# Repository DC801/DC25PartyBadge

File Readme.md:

# DC801_DC25PartyBadge
Party badge and BLE hardware board

Photo credits to [Cat Murdock](https://twitter.com/catmurd0ck), thank you!

# Hardware
 - **Rigado BMD-300** Bluetooth low energy based on a Nordic nRF52832
   - 16MHz ARM® Cortex™ M4F CPU, 512kB of flash memory, 64kB RAM
   - [https://www.rigado.com/product/bmd-300/](https://www.rigado.com/product/bmd-300/)
 ***
 - **Lots of I/O**
   - 2 RGB LEDs (_eyes_)
   - 7 yellow LEDs (_helmet_)
   - 6 red LEDs (_helmet wings_)
   - Speaker
   - 4 buttons
   - 2 capacitive 'touch' buttons (_for you to discover_)
   - SPI LCD screen
   - Selected pin breakouts
   - JTAG interface
   - Micro USB - for charging only
 ***
 - A MCP73831 LiPo battery charger
 - Kickass silkscreen

Board design is in Eagle

See the [Hardware](/Hardware) directory for more info, schematics and etc

# Software
Environment is Eclipse with the GNU ARM GCC
Need a J-Link Segger JTAG programmer
Uses the softdevice s132

See the [Software](/Software) directory for more info

# What's it do?

Awesome **things**, that's what!  See the [Software](Software) directory for more information.

# More info

Follow [@rushan_ee](http://twitter.com/rushan_ee) or [@hamster](http://twitter.com/hamster) for updates

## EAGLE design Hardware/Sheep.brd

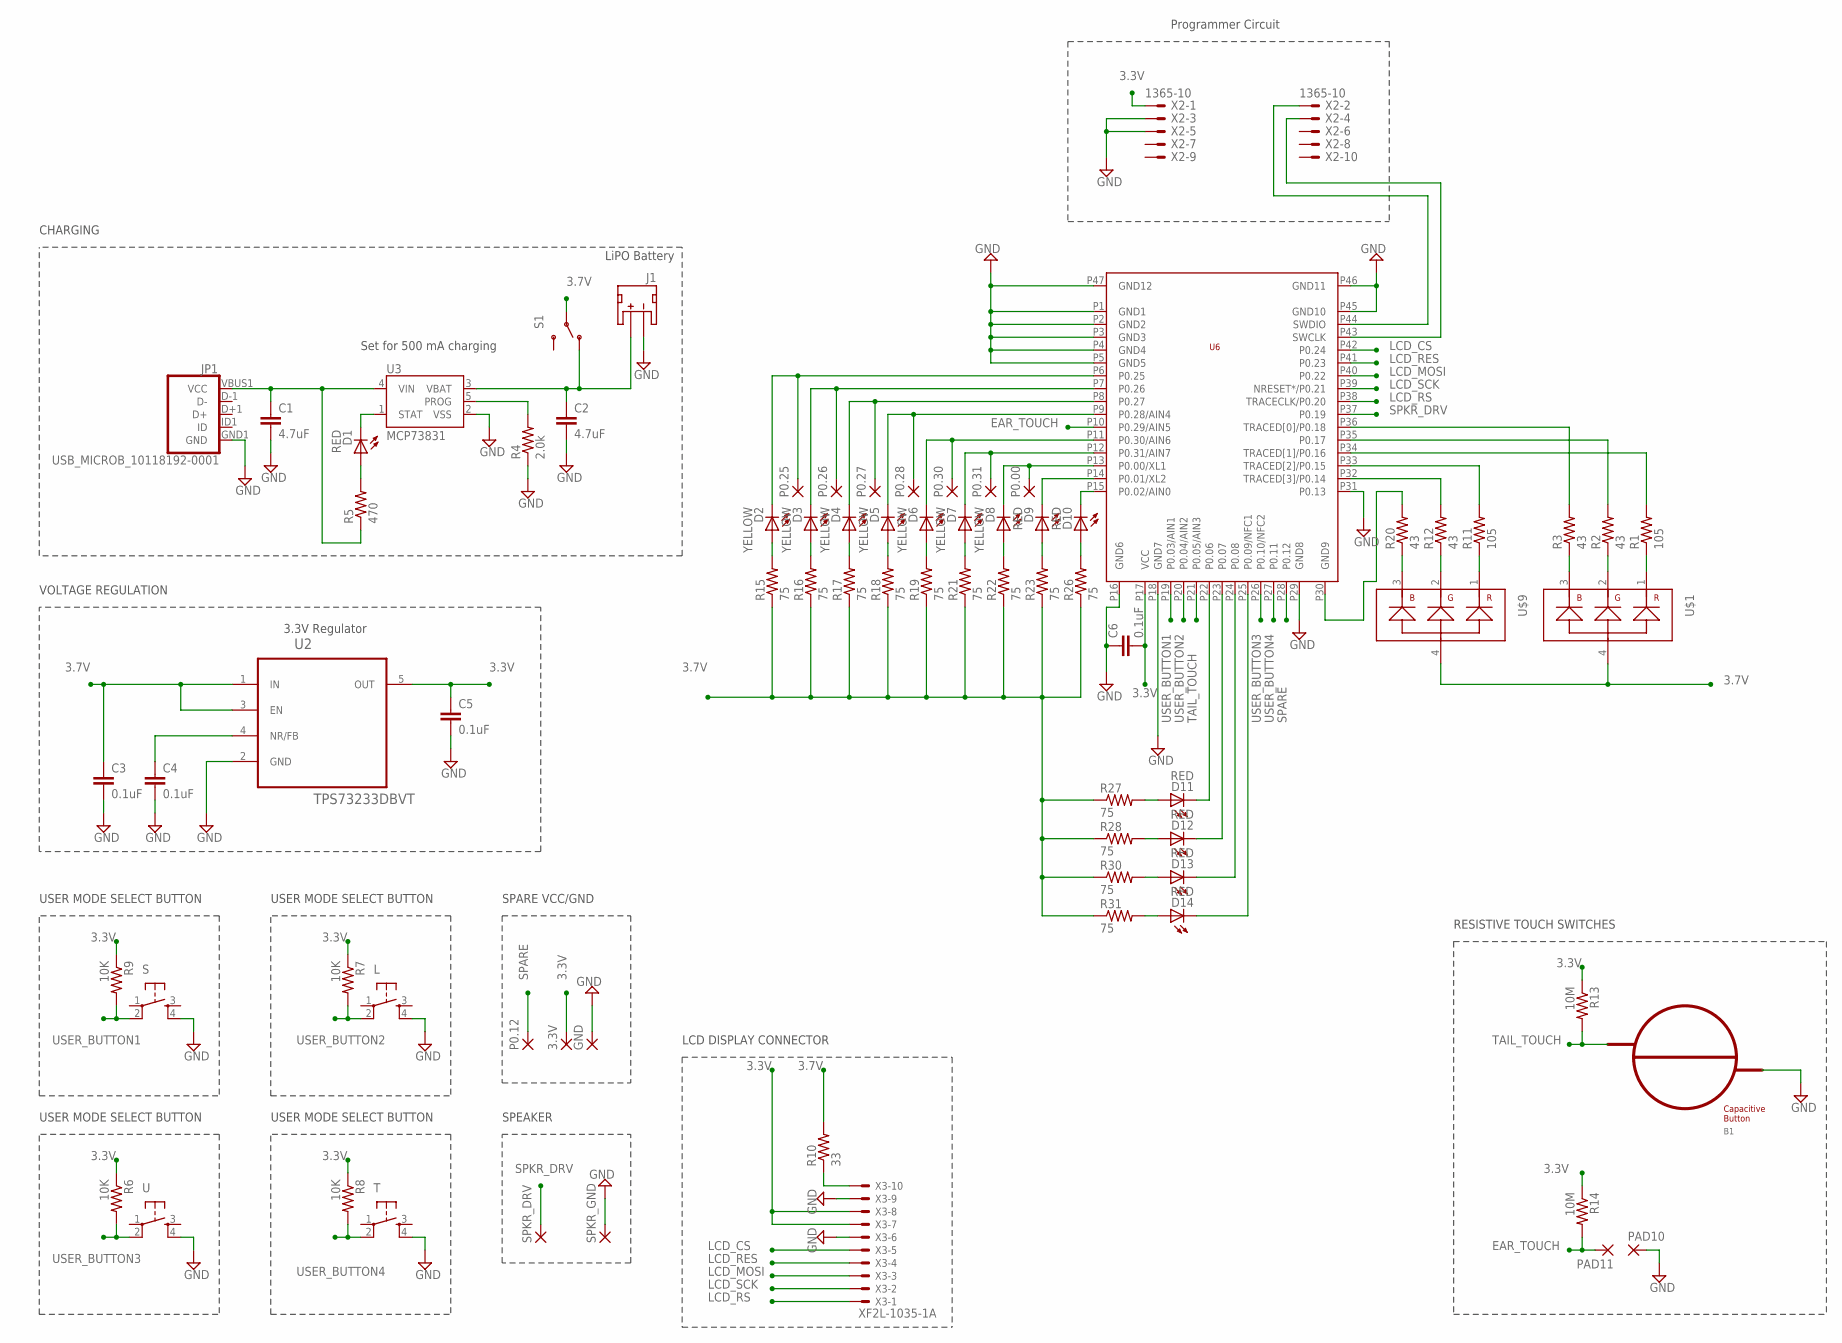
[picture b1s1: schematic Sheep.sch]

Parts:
3.3V: 1,6/0,8
B1: BUTTON_ACTIVE_DUAL; BUTTON_ACTIVE_DUAL_10MM
C1, C2: 4.7uF; 0603-CAP
C3, C4, C5, C6: 0.1uF; C0201
D1, D9, D10, D11, D12, D13, D14: RED; CHIP-LED0603
D2, D3, D4, D5, D6, D7, D8: YELLOW; CHIP-LED0603
GND: 1,6/0,8
J1: JST_2MM_MALE; JST-2-SMD
JP1: USB_MICROB_10118192-0001; USB-B-MICRO-SMD_V03
L: DTSM-6
P0.00, P0.12, P0.25, P0.26, P0.27, P0.28, P0.30, P0.31: 1,6/0,8
PAD10, PAD11: SMD5; SMD2,54-5,08
R1, R11: 105; R0201
R2, R3, R12, R20: 43; R0201
R4: 2.0k; R0201
R5: 470; R0201
R6, R7, R8, R9: 10K; R0201
R10: 33; R0201
R13, R14: 10M; R0201
R15, R16, R17, R18, R19, R21, R22, R23, R26, R27, R28, R30, R31: 75; R0201
S: DTSM-6
S1: SWITCH-SPDTSMD2; SWITCH-SPDT-SMD
SPKR_DRV: 1,6/0,8
SPKR_GND: 1,6/0,8
T: DTSM-6
U: DTSM-6
U2: TPS73233DBVT; SOT95P280X145-5N
U3: MCP73831; SOT23-5
U6: BMD-300
U$1, U$9: RGB; 0606
X2: 1365-10
X3: XF2L-1035-1A; 52745-1090

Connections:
3.3V: 3.3V.1, C5.1, C6.2, R6.1, R7.1, R8.1, R9.1, R13.1, R14.1, U2.5 (OUT), U6.P17 (VCC), X2.1, X3.7, X3.8
3.7V: C3.1, R10.2, R15.1, R16.1, R17.1, R18.1, R19.1, R21.1, R22.1, R23.1, R26.1, R27.1, R28.1, R30.1, R31.1, S1.2, U2.1 (IN), U2.3 (EN), U$1.4, U$9.4
5.0V: C1.1, JP1.VBUS1 (VCC), R5.1, U3.4 (VIN)
EAR_TOUCH: PAD11.1, R14.2, U6.P10 (P0.29/AIN5)
GND: B1.Q1, C1.2, C2.2, C3.2, C4.2, C5.2, C6.1, GND.1, J1.1 (-), JP1.GND1 (GND), L.4, PAD10.1, R4.1, S.4, SPKR_GND.1, T.4, U.4, U2.2 (GND), U3.2 (VSS), U6.P1 (GND1), U6.P2 (GND2), U6.P3 (GND3), U6.P4 (GND4), U6.P5 (GND5), U6.P16 (GND6), U6.P18 (GND7), U6.P29 (GND8), U6.P31 (P0.13), U6.P45 (GND10), U6.P46 (GND11), U6.P47 (GND12), X2.3, X2.5, X3.6, X3.9
LCD_CS: U6.P42 (P0.24), X3.5
LCD_MOSI: U6.P40 (P0.22), X3.3
LCD_RES: U6.P41 (P0.23), X3.4
LCD_RS: U6.P38 (TRACECLK/P0.20), X3.1
LCD_SCK: U6.P39 (NRESET*/P0.21), X3.2
unnamed: R2.2, U6.P35 (P0.17)
unnamed: R3.2, U6.P36 (TRACED[0]/P0.18)
unnamed: R11.2, U6.P33 (TRACED[2]/P0.15)
unnamed: D6.C, P0.30.1, U6.P11 (P0.30/AIN6)
unnamed: D2.C, P0.25.1, U6.P6 (P0.25)
unnamed: U6.P44 (SWDIO), X2.2
unnamed: R20.2, U6.P30 (GND9)
unnamed: D11.C, U6.P22 (P0.06)
unnamed: D12.C, U6.P23 (P0.07)
unnamed: U6.P43 (SWCLK), X2.4
unnamed: R1.2, U6.P34 (TRACED[1]/P0.16)
unnamed: R1.1, U$1.1
unnamed: R2.1, U$1.2
unnamed: R3.1, U$1.3
unnamed: D3.C, P0.26.1, U6.P7 (P0.26)
unnamed: D13.C, U6.P24 (P0.08)
unnamed: D5.C, P0.28.1, U6.P9 (P0.28/AIN4)
unnamed: D7.C, P0.31.1, U6.P12 (P0.31/AIN7)
unnamed: D8.C, P0.00.1, U6.P13 (P0.00/XL1)
unnamed: D9.C, U6.P14 (P0.01/XL2)
unnamed: D10.C, U6.P15 (P0.02/AIN0)
unnamed: D14.C, U6.P25 (P0.09/NFC1)
unnamed: R12.2, U6.P32 (TRACED[3]/P0.14)
unnamed: R4.2, U3.5 (PROG)
unnamed: D11.A, R27.2
unnamed: D12.A, R28.2
unnamed: D13.A, R30.2
unnamed: D14.A, R31.2
unnamed: R10.1, X3.10
unnamed: D1.A, R5.2
unnamed: D1.C, U3.1 (STAT)
unnamed: R11.1, U$9.1
unnamed: R12.1, U$9.2
unnamed: D2.A, R15.2
unnamed: D3.A, R16.2
unnamed: D4.A, R17.2
unnamed: D5.A, R18.2
unnamed: D6.A, R19.2
unnamed: D7.A, R21.2
unnamed: D8.A, R22.2
unnamed: C4.1, U2.4 (NR/FB)
unnamed: D9.A, R23.2
unnamed: D10.A, R26.2
unnamed: R20.1, U$9.3
unnamed: D4.C, P0.27.1, U6.P8 (P0.27)
SPARE: P0.12.1, U6.P28 (P0.12)
SPKR_DRV: SPKR_DRV.1, U6.P37 (P0.19)
TAIL_TOUCH: B1.Q2, R13.2, U6.P21 (P0.05/AIN3)
USER_BUTTON1: R9.2, S.2, U6.P19 (P0.03/AIN1)
USER_BUTTON2: L.2, R7.2, U6.P20 (P0.04/AIN2)
USER_BUTTON3: R6.2, U.2, U6.P26 (P0.10/NFC2)
USER_BUTTON4: R8.2, T.2, U6.P27 (P0.11)
VBAT1: C2.1, J1.2 (+), S1.1 (O), U3.3 (VBAT)

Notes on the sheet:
LiPO Battery
Set for 500 mA charging
3.3V Regulator
CHARGING
VOLTAGE REGULATION
USER MODE SELECT BUTTON
Programmer Circuit
LCD DISPLAY CONNECTOR
SPARE VCC/GND
SPEAKER
RESISTIVE TOUCH SWITCHES

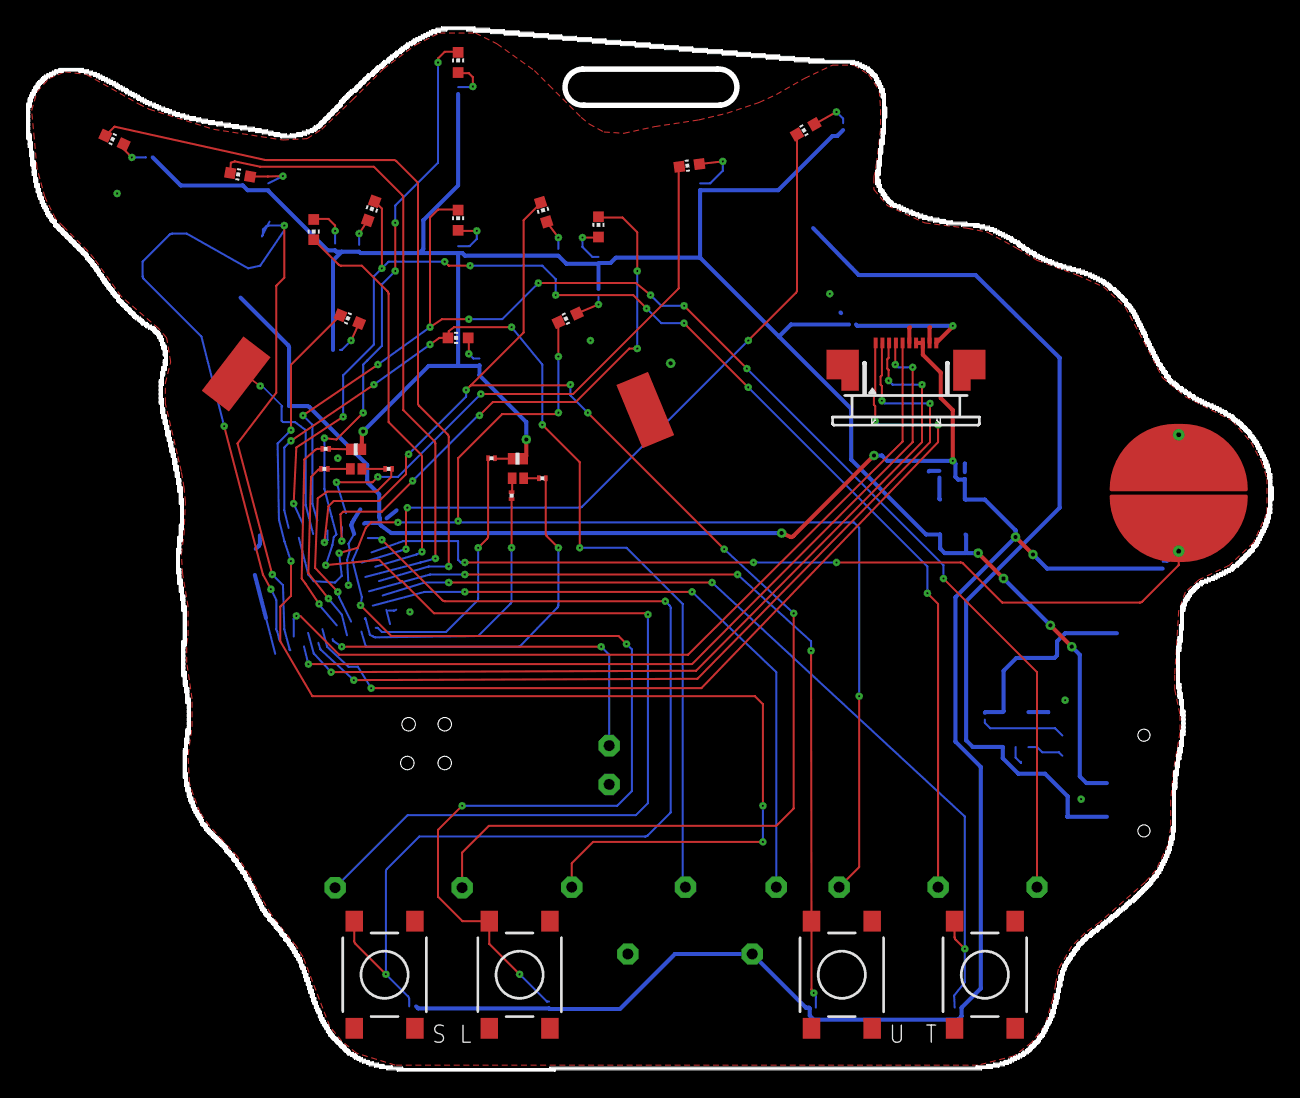
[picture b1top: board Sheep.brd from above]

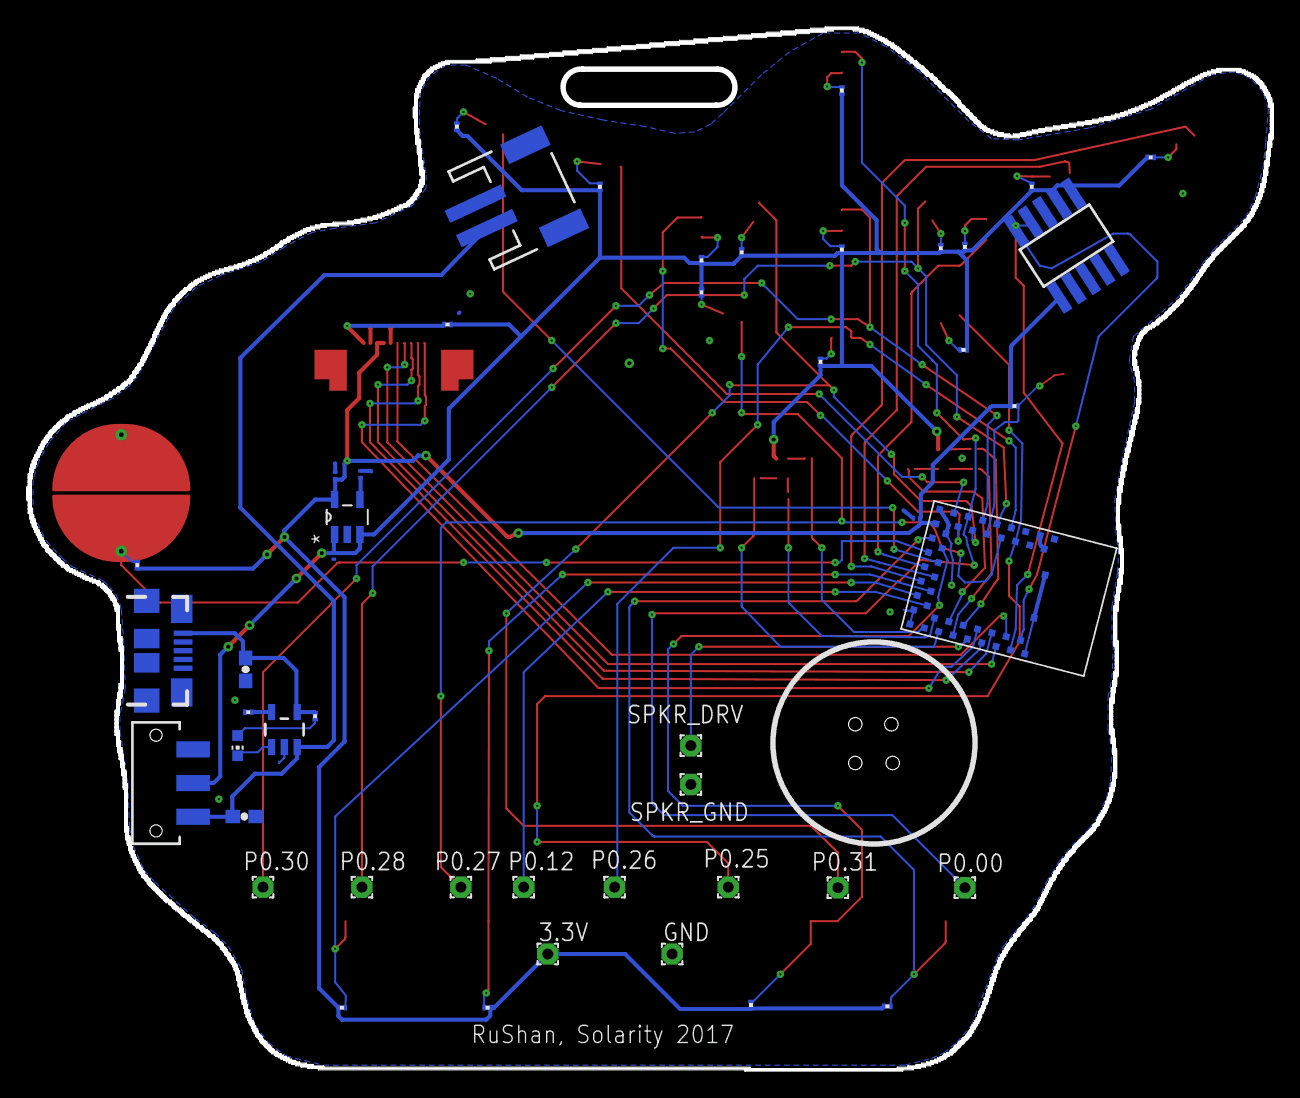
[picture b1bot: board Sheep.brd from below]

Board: 2 copper layers, 92.5 x 77.5 mm, 77 parts (48 on the bottom side), 63 nets.

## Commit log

2017-08-05 Adding the final software and hardware design for the DC25 party badge
2017-08-05 Adding a photo of the badge
2017-08-05 Fixed link to photo
2017-08-06 Fixed a buffer overflow Updated the makefile to allow a make flash out of the box
2017-08-06 Fixed detection of Queercon badges - they use more than 31 bytes advertisement, which means that part of the packet is received as a scan response
2017-08-07 Adding pdf versions of the schematic and board

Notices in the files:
parts and their libraries:
SparkFun-Connectors: Licensing: Creative Commons ShareAlike 4.0 International - https://creativecommons.org/licenses/by-sa/4.0
SparkFun: Licensing: CC v3.0 Share-Alike You are welcome to use this library for commercial purposes.
